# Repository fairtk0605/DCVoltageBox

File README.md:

# DC Voltage Box
This project aims to develop a circuit box capable of providing both positive and negative DC voltage outputs.
This circuit box supports two output modes. One mode provides a relatively low current output of approximately }2V DC. The other mode delivers a higher current DC output ranging from 3V to 5V. The high-current mode can be turned ON and OFF via microcontroller control.

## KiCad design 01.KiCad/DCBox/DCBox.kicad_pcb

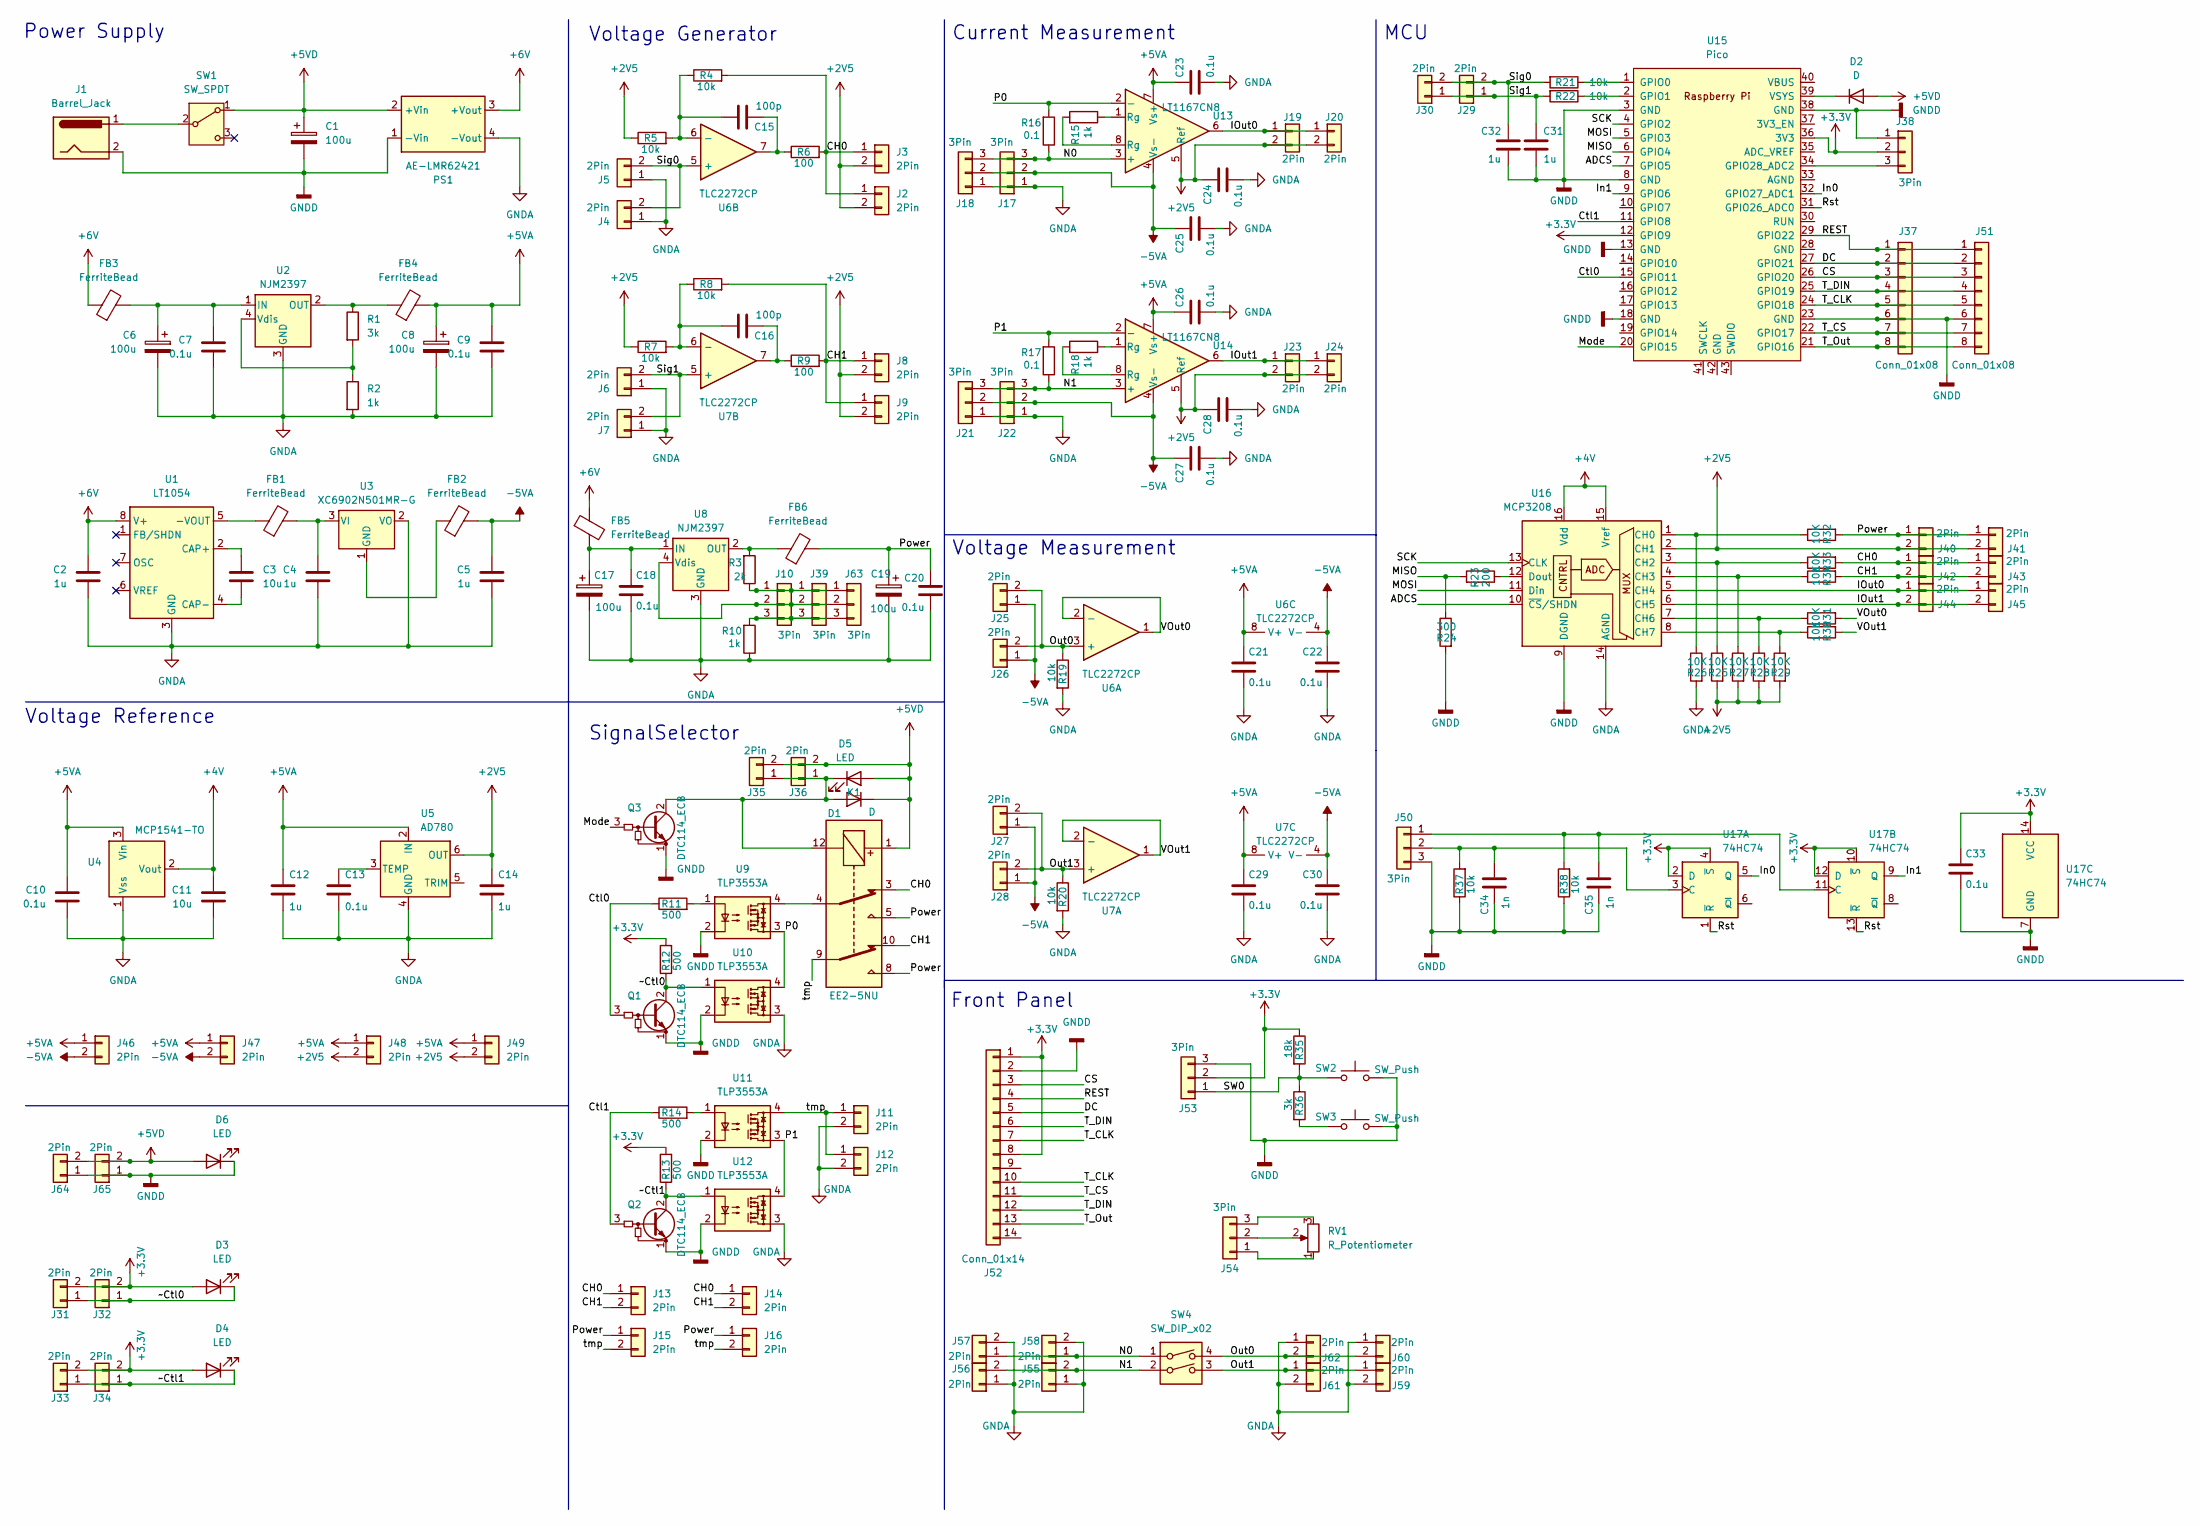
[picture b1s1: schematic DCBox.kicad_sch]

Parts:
C1, C6, C8, C17, C19: 100u; CP_Radial_D5.0mm_P2.50mm
C2, C4, C5, C12, C14, C31, C32: 1u; C_Disc_D3.0mm_W2.0mm_P2.50mm
C3, C11: 10u; C_Disc_D4.3mm_W1.9mm_P5.00mm
C7, C9, C10, C13, C18, C20, C21, C22, C23, C24, C25, C26, C27, C28, C29, C30, C33: 0.1u; C_Disc_D3.0mm_W2.0mm_P2.50mm
C15, C16: 100p; C_Disc_D3.0mm_W2.0mm_P2.50mm
C34, C35: 1n; C_Disc_D3.0mm_W2.0mm_P2.50mm
D1: D; D_DO-34_SOD68_P2.54mm_Vertical_KathodeUp
D2: D; D_DO-34_SOD68_P10.16mm_Horizontal
D3, D4, D5, D6: LED; LED_D3.0mm
FB1, FB3, FB4, FB6: FerriteBead; L_Axial_L5.3mm_D2.2mm_P2.54mm_Vertical_Vishay_IM-1
FB2: FerriteBead; L_Axial_L5.3mm_D2.2mm_P7.62mm_Horizontal_Vishay_IM-1
FB5: FerriteBead; L_Axial_L7.0mm_D3.3mm_P5.08mm_Vertical_Fastron_MICC
J1: Barrel_Jack; BarrelJack_CUI_PJ-102AH_Horizontal
J2, J3, J4, J5, J6, J7, J8, J9, J11, J12, J13, J14, J15, J16, J19, J20, J23, J24, J25, J26, J27, J28, J29, J30, J31, J32, J33, J34, J35, J36, J40, J41, J42, J43, J44, J45, J46, J47, J48, J49, J55, J56, J57, J58, J59, J60, J61, J62, J64, J65: 2Pin; PinHeader_1x02_P2.54mm_Vertical
J10, J17, J18, J21, J22, J38, J39, J53, J54, J63: 3Pin; PinHeader_1x03_P2.54mm_Vertical
J37, J51: Conn_01x08; PinHeader_1x08_P2.54mm_Vertical
J50: 3Pin; PinHeader_1x03_P2.54mm_Horizontal
J52: Conn_01x14; PinHeader_1x14_P2.54mm_Vertical
K1: EE2-5NU; Relay_DPDT_Kemet_EC2_NU
PS1: AE-LMR62421
Q1, Q2, Q3: DTC114_ECB; TO-92L_Inline_Wide
R1: 3k; R_Axial_DIN0204_L3.6mm_D1.6mm_P5.08mm_Vertical
R2, R10: 1k; R_Axial_DIN0204_L3.6mm_D1.6mm_P2.54mm_Vertical
R3: 2k; R_Axial_DIN0204_L3.6mm_D1.6mm_P5.08mm_Vertical
R4, R5, R7, R8, R19, R20, R21, R22, R37, R38: 10k; R_Axial_DIN0204_L3.6mm_D1.6mm_P2.54mm_Vertical
R6, R9: 100; R_Axial_DIN0204_L3.6mm_D1.6mm_P2.54mm_Vertical
R11, R12, R13, R14: 500; R_Axial_DIN0204_L3.6mm_D1.6mm_P2.54mm_Vertical
R15, R18: 1k; R_Axial_DIN0204_L3.6mm_D1.6mm_P5.08mm_Vertical
R16, R17: 0.1; R_Axial_DIN0204_L3.6mm_D1.6mm_P2.54mm_Vertical
R23: 200; R_Axial_DIN0204_L3.6mm_D1.6mm_P2.54mm_Vertical
R24: 300; R_Axial_DIN0204_L3.6mm_D1.6mm_P7.62mm_Horizontal
R25, R26, R27, R28, R29, R30, R31, R32, R33, R34: 10K; R_0805_2012Metric
R35: 18k; R_Axial_DIN0204_L3.6mm_D1.6mm_P2.54mm_Vertical
R36: 3k; R_Axial_DIN0204_L3.6mm_D1.6mm_P2.54mm_Vertical
RV1: R_Potentiometer; Potentiometer_ACP_CA9-H5_Horizontal
SW1: SW_SPDT; PinHeader_1x03_P2.54mm_Vertical
SW2, SW3: SW_Push; SW_PUSH_6mm
SW4: SW_DIP_x02; SW_DIP_SPSTx02_Slide_9.78x7.26mm_W7.62mm_P2.54mm
U1: LT1054; DIP-8_W7.62mm
U2, U8: NJM2397; TO-220-4_Vertical
U3: XC6902N501MR-G; SOT-23
U4: MCP1541-TO; TO-92_Inline_Wide
U5: AD780; DIP-8_W7.62mm
U6, U7: TLC2272CP; DIP-8_W7.62mm
U9, U10, U11, U12: TLP3553A; DIP-4_W7.62mm
U13, U14: LT1167CN8; DIP-8_W7.62mm
U15: Pico; RPi_Pico_TH
U16: MCP3208; DIP-16_W7.62mm
U17: 74HC74; DIP-14_W7.62mm

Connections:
+2V5: C14.1, C24.1, C28.1, J2.2, J3.2, J8.2, J9.2, J19.2, J20.2, J23.2, J24.2, J40.2, J41.2, J48.2, J49.2, R5.1, R7.1, R25.2, R27.2, R28.2, R29.2, U5.6 (OUT), U13.5 (Ref), U14.5 (Ref), U16.2 (CH1)
+3.3V: C33.1, D3.2 (A), D4.2 (A), J31.2, J32.2, J33.2, J34.2, J38.2, J52.1, J52.8, J53.2, R12.2, R13.2, R35.1, U15.12 (GPIO9), U15.36 (3V3), U17.2 (D), U17.4 (~S), U17.10 (~S), U17.12 (D), U17.14 (VCC)
+4V: C11.1, U4.2 (Vout), U16.15 (Vref), U16.16 (Vdd)
+5VA: C8.1, C9.1, C10.1, C12.1, C21.1, C23.1, C26.1, C29.1, FB4.2, J46.1, J47.1, J48.1, J49.1, U4.3 (Vin), U5.2 (IN), U6.8 (V+), U7.8 (V+), U13.7 (Vs+), U14.7 (Vs+)
+5VD: C1.1, D1.1 (K), D2.2 (A), D5.2 (A), D6.2 (A), J35.2, J36.2, J64.2, J65.2, K1.1, PS1.2 (+Vin), SW1.1 (A)
+6V: C2.1, FB3.1, FB5.1, PS1.3 (+Vout), U1.8 (V+)
-5VA: C5.1, C22.1, C25.1, C27.1, C30.1, FB2.2, J17.2, J18.2, J21.2, J22.2, J25.1, J26.1, J27.1, J28.1, J46.2, J47.2, U6.4 (V-), U7.4 (V-), U13.4 (Vs-), U14.4 (Vs-)
/ADCS: U15.7 (GPIO5), U16.10 (~CS/SHDN)
/CH0: J2.1, J3.1, J13.1, J14.1, J42.1, J43.1, K1.3, R4.2, R6.2, R33.2
/CH1: J8.1, J9.1, J13.2, J14.2, J42.2, J43.2, K1.10, R8.2, R9.2, R34.2
/CS: J37.3, J51.3, J52.3, U15.26 (GPIO20)
/Ctl0: Q1.3 (B), R11.1, U15.15 (GPIO11)
/Ctl1: Q2.3 (B), R14.1, U15.11 (GPIO8)
/DC: J37.2, J51.2, J52.5, U15.27 (GPIO21)
/IOut0: J19.1, J20.1, J44.1, J45.1, U13.6, U16.5 (CH4)
/IOut1: J23.1, J24.1, J44.2, J45.2, U14.6, U16.6 (CH5)
/In0: U15.32 (GPIO27_ADC1), U17.5 (Q)
/In1: U15.9 (GPIO6), U17.9 (Q)
/MISO: R23.2, R24.1, U15.6 (GPIO4)
/MOSI: U15.5 (GPIO3), U16.11 (Din)
/Mode: Q3.3 (B), U15.20 (GPIO15)
/N0: J17.3, J18.3, J57.1, J58.1, R16.1, SW4.1, U13.3 (+)
/N1: J21.3, J22.3, J55.2, J56.2, R17.1, SW4.2, U14.3 (+)
/Out0: J25.2, J26.2, J60.2, J62.2, R19.1, SW4.4, U6.3 (+)
/Out1: J27.2, J28.2, J59.1, J61.1, R20.1, SW4.3, U7.3 (+)
/P0: R16.2, U9.3, U10.4, U13.2 (-)
/P1: R17.2, U11.3, U12.4, U14.2 (-)
/Power: C19.1, C20.1, FB6.2, J15.1, J16.1, J40.1, J41.1, K1.5, K1.8, R32.2
/REST: J37.1, J51.1, J52.4, U15.29 (GPIO22)
/Rst: U15.31 (GPIO26_ADC0), U17.1 (~R), U17.13 (~R)
/SCK: U15.4 (GPIO2), U16.13 (CLK)
/SW0: J53.1, R35.2, R36.1, SW2.1
/T_CLK: J37.5, J51.5, J52.7, J52.10, U15.24 (GPIO18)
/T_CS: J37.7, J51.7, J52.11, U15.22 (GPIO17)
/T_DIN: J37.4, J51.4, J52.6, J52.12, U15.25 (GPIO19)
/T_Out: J37.8, J51.8, J52.13, U15.21 (GPIO16)
/VOut0: R31.2, U6.1, U6.2 (-)
/VOut1: R30.2, U7.1, U7.2 (-)
/tmp: J11.1, J12.1, J15.2, J16.2, K1.9, U11.4
/~Ctl0: D3.1 (K), J31.1, J32.1, Q1.2 (C), R12.1, U10.1
/~Ctl1: D4.1 (K), J33.1, J34.1, Q2.2 (C), R13.1, U12.1
GNDA: C2.2, C4.2, C5.2, C6.2, C7.2, C8.2, C9.2, C10.2, C11.2, C12.2, C13.2, C14.2, C17.2, C18.2, C19.2, C20.2, C21.2, C22.2, C23.2, C24.2, C25.2, C26.2, C27.2, C28.2, C29.2, C30.2, J4.1, J5.1, J6.1, J7.1, J11.2, J12.2, J17.1, J18.1, J21.1, J22.1, J55.1, J56.1, J57.2, J58.2, J59.2, J60.1, J61.2, J62.1, PS1.4 (-Vout), R2.2, R10.1, R19.2, R20.2, R26.2, U1.3 (GND), U2.3 (GND), U3.2 (VO), U4.1 (Vss), U5.4 (GND), U8.3 (GND), U10.3, U12.3, U16.14 (AGND)
GNDD: C1.2, C31.2, C32.2, C33.2, C34.1, C35.1, D6.1 (K), J1.2, J37.6, J38.1, J50.3, J51.6, J52.2, J53.3, J64.1, J65.1, PS1.1 (-Vin), Q1.1 (E), Q2.1 (E), Q3.1 (E), R24.2, R37.1, R38.1, SW2.2, SW3.2, U9.2, U10.2, U11.2, U12.2, U15.3 (GND), U15.8 (GND), U15.13 (GND), U15.18 (GND), U15.23 (GND), U15.38 (GND), U16.9 (DGND), U17.7 (GND)
unnamed: C15.1, R6.1, U6.7
unnamed: C16.1, R9.1, U7.7
unnamed: D1.2 (A), D5.1 (K), J35.1, J36.1, K1.12, Q3.2 (C)
unnamed: D2.1 (K), U15.39 (VSYS)
unnamed: J10.1, J39.1, J63.1, R3.1
unnamed: J10.2, J39.2, J63.2, U8.4 (Vdis)
unnamed: J10.3, J39.3, J63.3, R10.2
unnamed: J38.3, U15.34 (GPIO28_ADC2)
unnamed: C35.2, J50.1, R38.2, U17.11 (C)
unnamed: C34.2, J50.2, R37.2, U17.3 (C)
unnamed: J54.1, RV1.1
unnamed: J54.2, RV1.2
unnamed: J54.3, RV1.3
unnamed: K1.4, U9.4
unnamed: R11.2, U9.1
unnamed: R14.2, U11.1
unnamed: R15.1, U13.1 (Rg)
unnamed: R15.2, U13.8 (Rg)
unnamed: R18.1, U14.1 (Rg)
unnamed: R18.2, U14.8 (Rg)
unnamed: R36.2, SW3.1
unnamed: J1.1, SW1.2 (B)
unnamed: FB1.1, U1.5 (-VOUT)
unnamed: C3.1, U1.2 (CAP+)
unnamed: C3.2, U1.4 (CAP-)
unnamed: C6.1, C7.1, FB3.2, U2.1 (IN)
unnamed: FB4.1, R1.1, U2.2 (OUT)
unnamed: R1.2, R2.1, U2.4 (Vdis)
unnamed: FB2.1, U3.1 (GND)
unnamed: C4.1, FB1.2, U3.3 (VI)
unnamed: C13.1, U5.3 (TEMP)
unnamed: C15.2, R4.1, R5.2, U6.6 (-)
unnamed: C16.2, R7.2, R8.1, U7.6 (-)
unnamed: C17.1, C18.1, FB5.2, U8.1 (IN)
unnamed: FB6.1, R3.2, U8.2 (OUT)
unnamed: R21.1, U15.1 (GPIO0)
unnamed: R22.1, U15.2 (GPIO1)
unnamed: R26.1, R32.1, U16.1 (CH0)
unnamed: R25.1, R33.1, U16.3 (CH2)
unnamed: R27.1, R34.1, U16.4 (CH3)
unnamed: R28.1, R31.1, U16.7 (CH6)
unnamed: R29.1, R30.1, U16.8 (CH7)
unnamed: R23.1, U16.12 (Dout)

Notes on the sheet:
Voltage Generator
Power Supply
SignalSelector
Voltage Reference
Front Panel
Voltage Measurement
MCU
Current Measurement

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
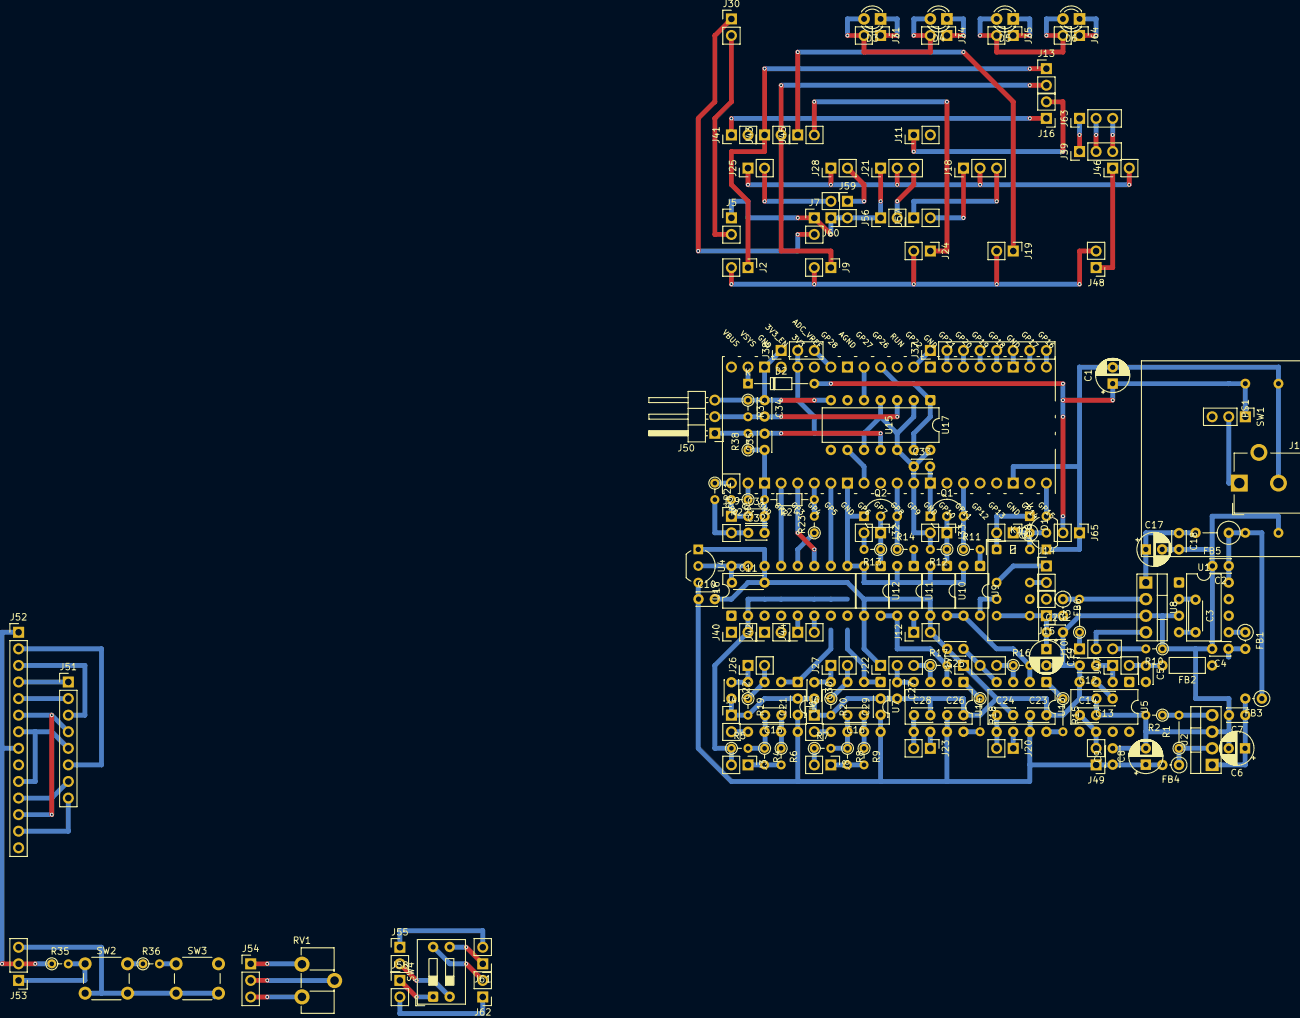
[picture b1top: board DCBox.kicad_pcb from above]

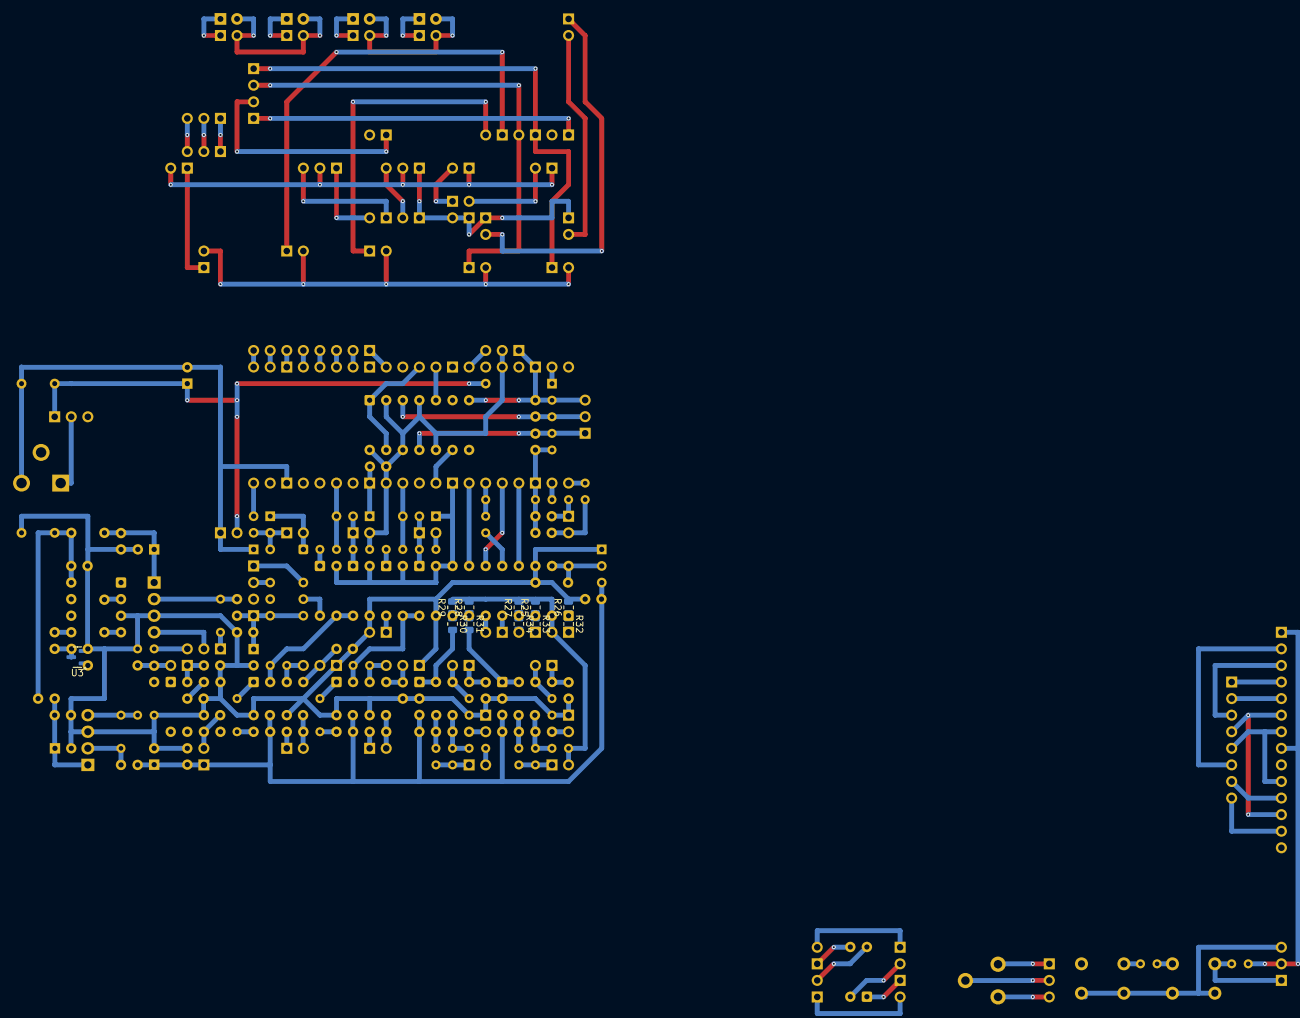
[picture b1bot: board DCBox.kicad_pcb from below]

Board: 2 copper layers, 177 parts (11 on the bottom side), 88 nets.

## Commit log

2025-04-07 KiCad Done
2025-04-07 Added First Simple ReadMe
